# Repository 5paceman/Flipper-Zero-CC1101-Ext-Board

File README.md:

# Flipper Zero External CC1101 PCB

This is a simple design for a PCB to connect to a Flipper Zero to add an external CC1101 module with a better antenna. It includes simple circuit protection for the CC1101 module as well as pins on the right hand side for further development. 

Here is the current PCB design:

Here is the current schematic design: 

KiCad files can be found in CC101ExtBoard folder

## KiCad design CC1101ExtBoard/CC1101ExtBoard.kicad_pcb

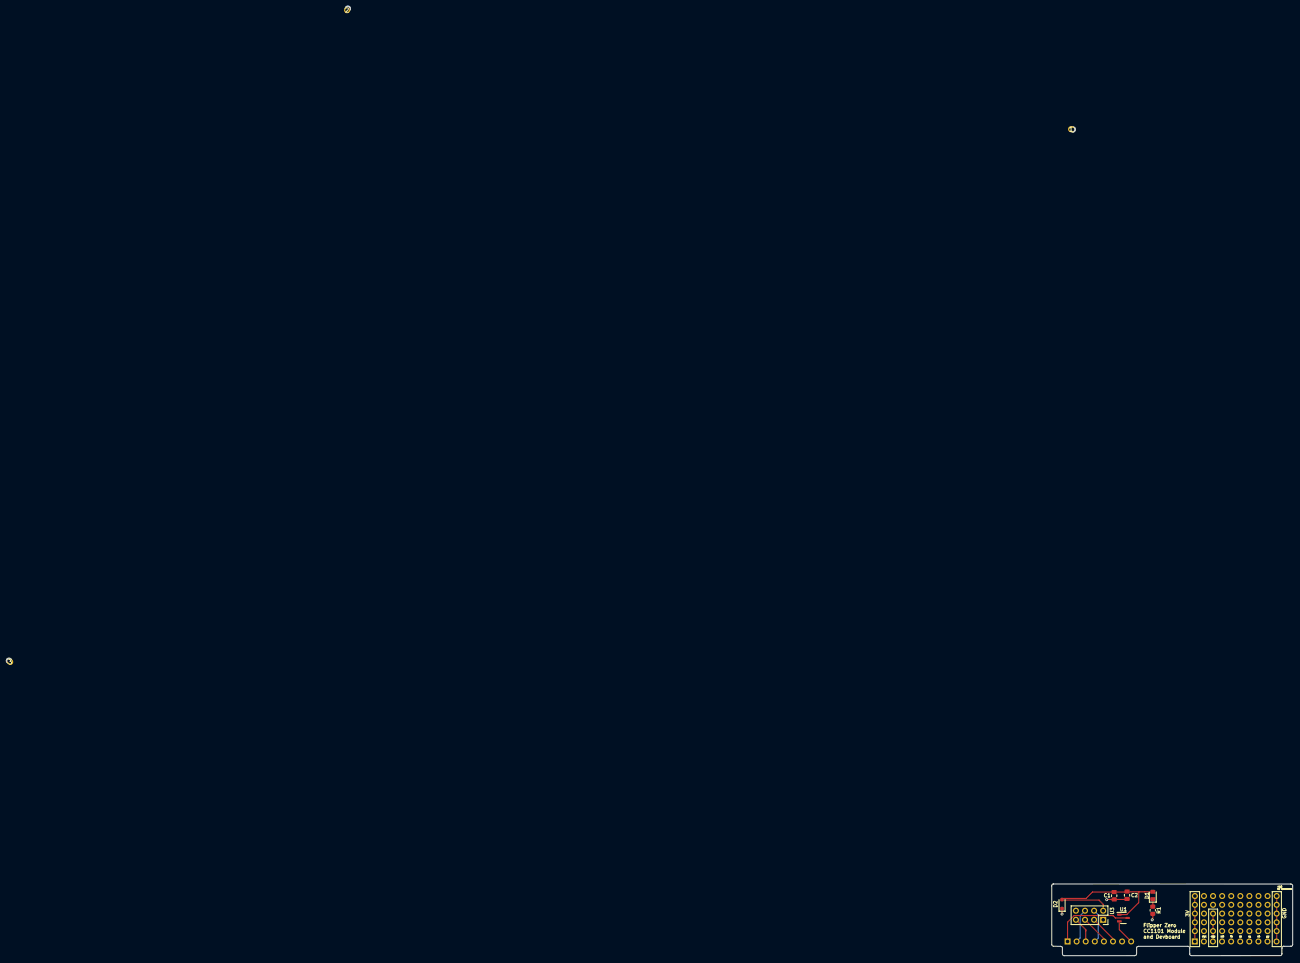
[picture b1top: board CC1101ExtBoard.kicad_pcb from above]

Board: 2 copper layers, 67.3 x 20.0 mm, 10 parts (0 on the bottom side), 3 nets.

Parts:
1, 2, 3: (no value)
C1: 0.1uF; C_0805_2012Metric_Pad1.18x1.45mm_HandSolder
C2: 10uF; C_0805_2012Metric_Pad1.18x1.45mm_HandSolder
D1: LED; LED_0805_2012Metric_Pad1.15x1.40mm_HandSolder
D2: Zener 3.6v; D_SOD-323_HandSoldering
R1: 10 Ohms; R_0805_2012Metric_Pad1.20x1.40mm_HandSolder
U1: LF33CV; SOT-23-3
U3: PinSocket_2x04_P2.54mm_Vertical

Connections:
GND: C1.1, C2.1, D2.1 (K), R1.2, U1.2 (GND), U3.1 (GND)
unnamed: D1.1 (K), R1.1
VCC: C1.2, C2.2, D1.2 (A), D2.2 (A), U1.1 (VI), U1.3 (VO), U3.2 (VCC)

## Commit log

2023-05-21 Added readme
2023-05-26 updated to KiCad
